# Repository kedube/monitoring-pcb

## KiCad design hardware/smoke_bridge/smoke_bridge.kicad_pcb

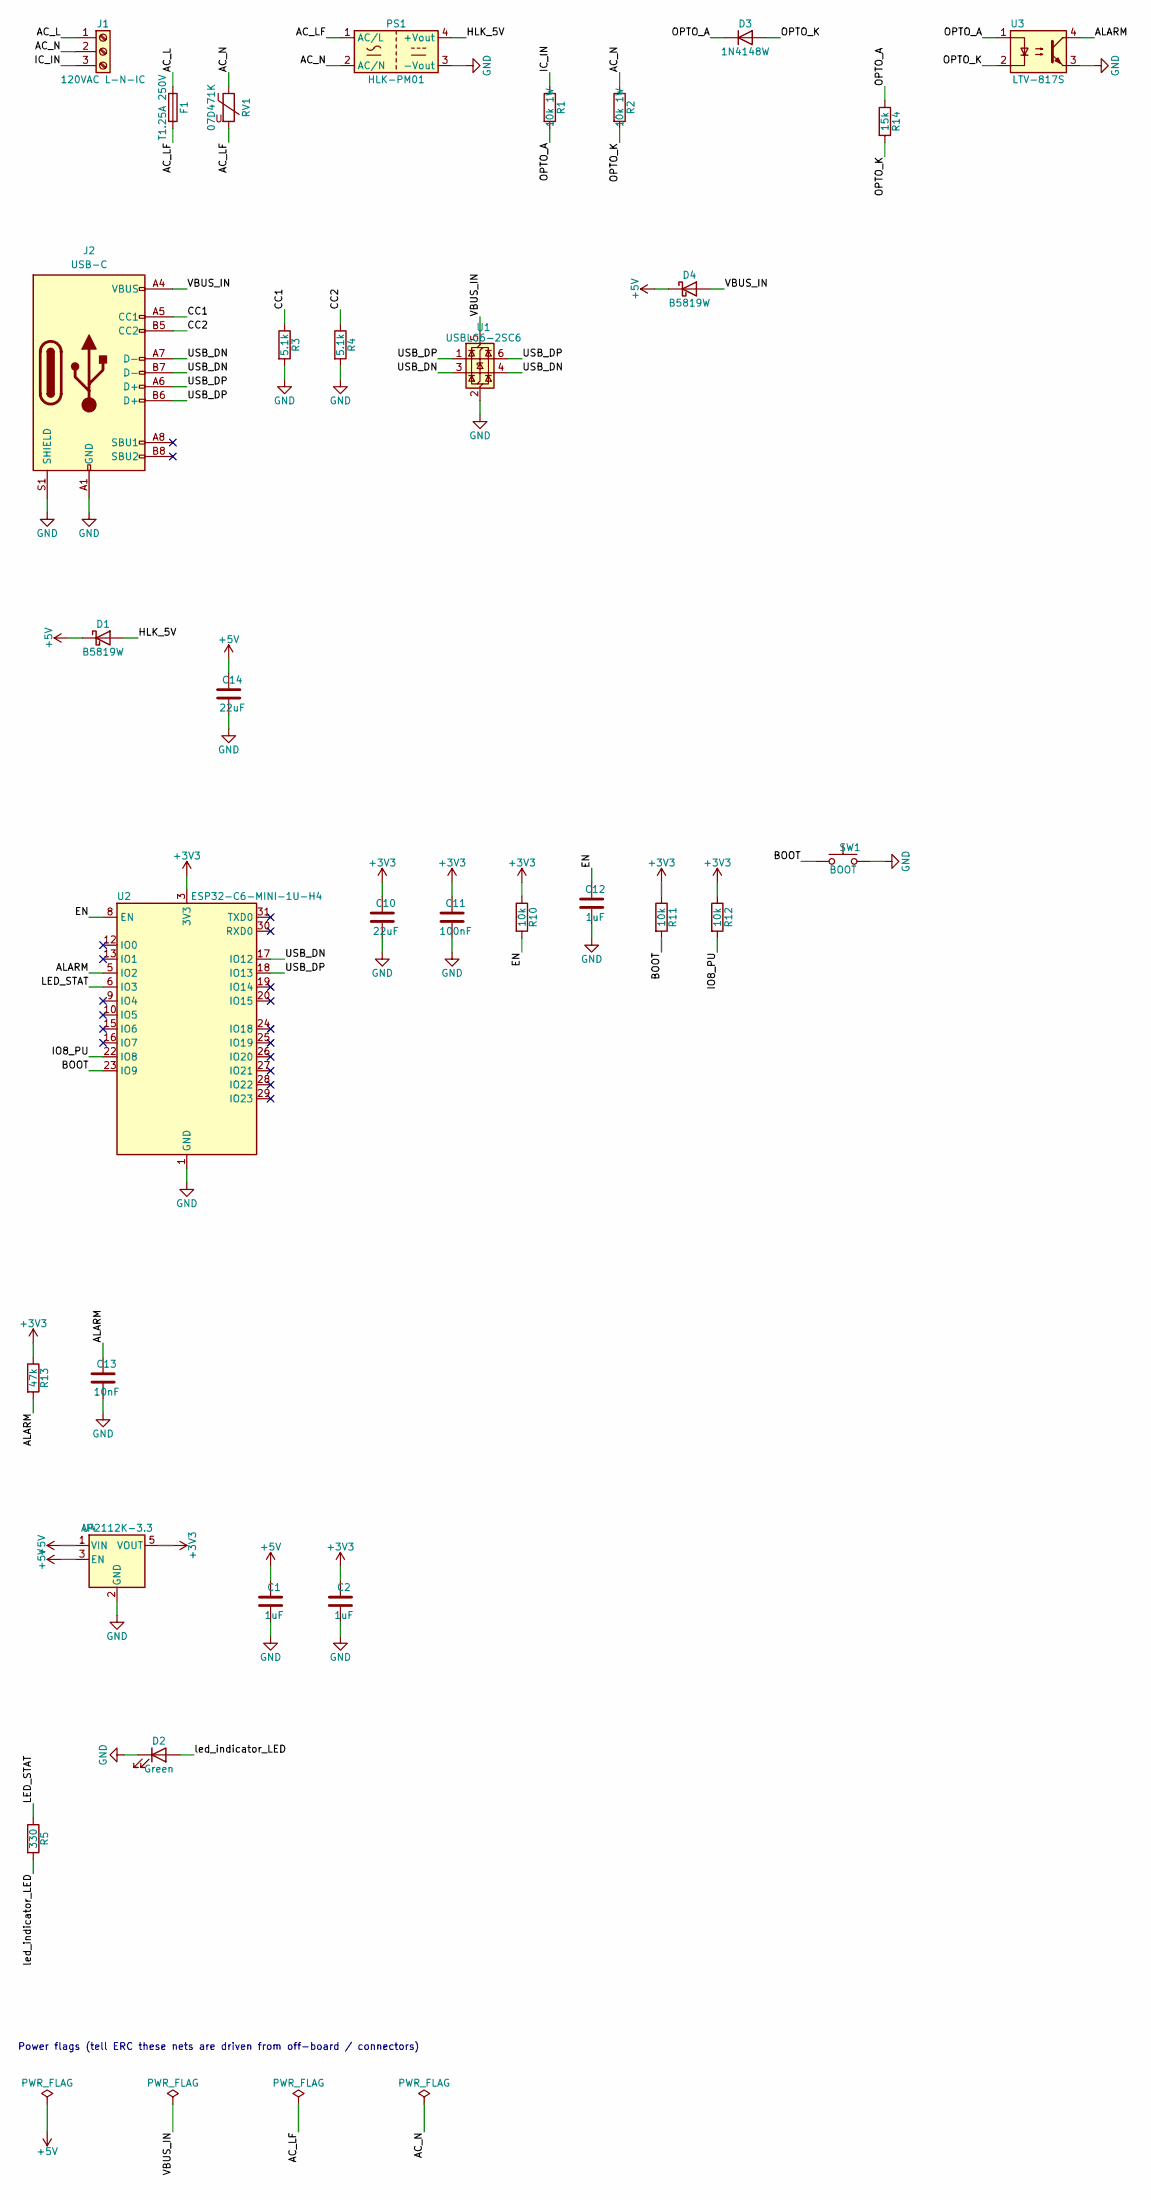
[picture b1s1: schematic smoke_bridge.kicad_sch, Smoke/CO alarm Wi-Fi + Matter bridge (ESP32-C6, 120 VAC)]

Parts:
C1, C2: 1uF; C_0603_1608Metric; LCSC C15849
C10, C14: 22uF; C_1206_3216Metric; LCSC C12891
C11: 100nF; C_0402_1005Metric; LCSC C307331
C12: 1uF; C_0402_1005Metric; LCSC C52923
C13: 10nF; C_0402_1005Metric; LCSC C15195
D1, D4: B5819W; D_SOD-123; LCSC C8598
D2: Green; LED_0805_2012Metric; LCSC C2297
D3: 1N4148W; D_SOD-123; LCSC C81598
F1: T1.25A 250V; Fuse_Littelfuse_395Series; MPN 2010T1.25A250V; LCSC C354901
J1: 120VAC L-N-IC; Terminal_3P_5.08_L-N-IC; MPN DB128L-5.08-3P-BK-S; LCSC C430602
J2: USB-C; USB_C_Receptacle_HRO_TYPE-C-31-M-12; LCSC C165948
PS1: HLK-PM01; HLK-PM01_IsolationBarrier; LCSC C209903
R1, R2: 10k 1W; R_2512_6332Metric; Voltage 200V; LCSC C25718
R3, R4: 5.1k; R_0603_1608Metric; LCSC C23186
R5: 330; R_0603_1608Metric; LCSC C23138
R10, R11, R12: 10k; R_0402_1005Metric; LCSC C25744
R13: 47k; R_0402_1005Metric; LCSC C25792
R14: 15k; R_0603_1608Metric; LCSC C22809
RV1: 07D471K; C_Disc_D7.5mm_W5.0mm_P5.00mm; LCSC C49072860
SW1: BOOT; SW_SPST_PTS810; MPN PTS810SJG250SMTRLFS; LCSC C221895
U1: USBLC6-2SC6; SOT-23-6; LCSC C7519
U2: ESP32-C6-MINI-1U-H4; ESP32-C6-MINI-1U; LCSC C20627095
U3: LTV-817S; SMDIP-4_W9.53mm; MPN LTV-817S-TA1-C; LCSC C109227
U4: AP2112K-3.3; SOT-23-5; LCSC C51118

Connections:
+3V3: C2.1, C10.1, C11.1, R10.1, R11.1, R12.1, R13.1, U2.3 (3V3), U4.5 (VOUT)
+5V: C1.1, C14.1, D1.1 (K), D4.1 (K), U4.1 (VIN), U4.3 (EN)
/AC_L: F1.1, J1.1
/AC_LF: F1.2, PS1.1 (AC/L), RV1.2
/AC_N: J1.2, PS1.2 (AC/N), R2.1, RV1.1
/ALARM: C13.1, R13.2, U2.5 (IO2), U3.4
/BOOT: R11.2, SW1.1, U2.23 (IO9)
/CC1: J2.A5 (CC1), R3.1
/CC2: J2.B5 (CC2), R4.1
/EN: C12.1, R10.2, U2.8 (EN)
/HLK_5V: D1.2 (A), PS1.4 (+Vout)
/IC_IN: J1.3, R1.1
/IO8_PU: R12.2, U2.22 (IO8)
/LED_STAT: R5.1, U2.6 (IO3)
/OPTO_A: D3.1 (K), R1.2, R14.1, U3.1
/OPTO_K: D3.2 (A), R2.2, R14.2, U3.2
/USB_DN: J2.A7 (D-), J2.B7 (D-), U1.3 (I/O2), U1.4 (I/O2), U2.17 (IO12)
/USB_DP: J2.A6 (D+), J2.B6 (D+), U1.1 (I/O1), U1.6 (I/O1), U2.18 (IO13)
/VBUS_IN: D4.2 (A), J2.A4 (VBUS), J2.A9 (VBUS), J2.B4 (VBUS), J2.B9 (VBUS), U1.5 (VBUS)
/led_indicator_LED: D2.2 (A), R5.2
GND: C1.2, C2.2, C10.2, C11.2, C12.2, C13.2, C14.2, D2.1 (K), J2.A1 (GND), J2.A12 (GND), J2.B1 (GND), J2.B12 (GND), J2.S1 (SHIELD), PS1.3 (-Vout), R3.2, R4.2, SW1.2, U1.2 (GND), U2.1 (GND), U2.2 (GND), U2.11 (GND), U2.14 (GND), U2.36 (GND), U2.37 (GND), U2.38 (GND), U2.39 (GND), U2.40 (GND), U2.41 (GND), U2.42 (GND), U2.43 (GND), U2.44 (GND), U2.45 (GND), U2.46 (GND), U2.47 (GND), U2.48 (GND), U2.49 (GND), U2.50 (GND), U2.51 (GND), U2.52 (GND), U2.53 (GND), U3.3, U4.2 (GND)

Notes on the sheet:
Power flags (tell ERC these nets are driven from off-board / connectors)

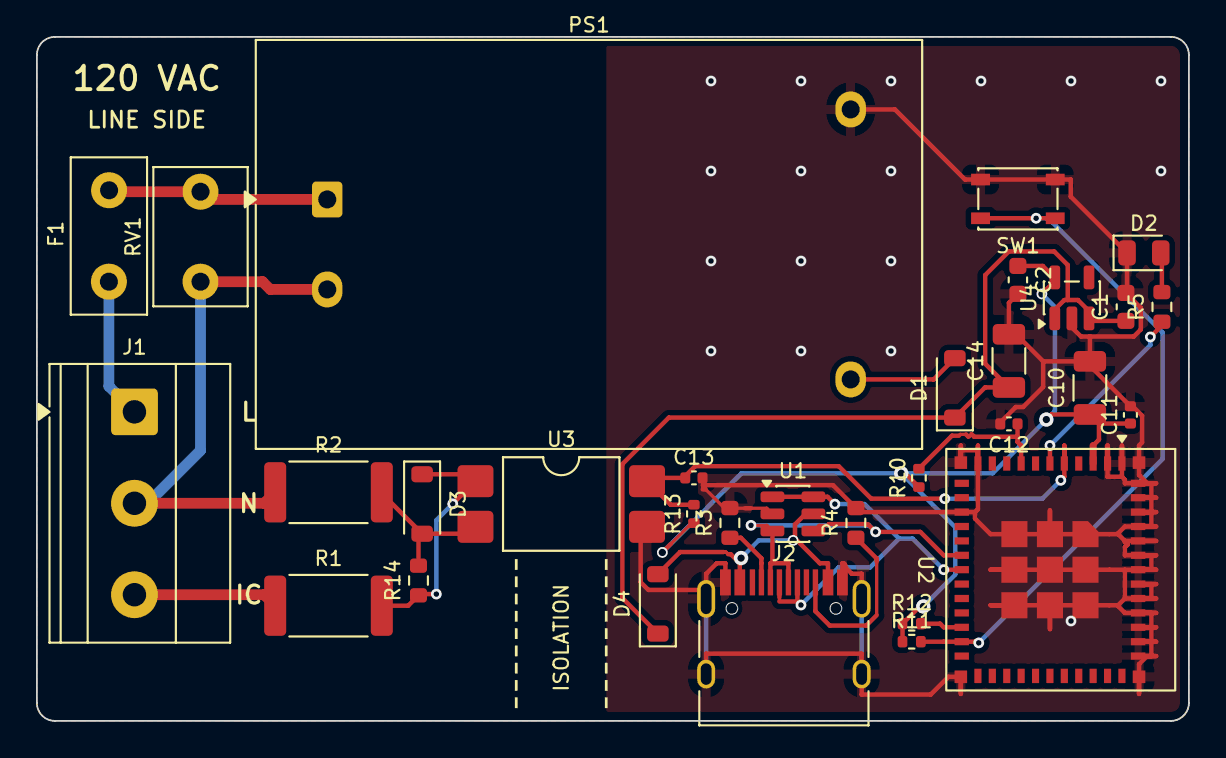
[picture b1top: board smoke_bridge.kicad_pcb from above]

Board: 2 copper layers, 64.0 x 38.0 mm, 31 parts (0 on the bottom side), 21 nets.

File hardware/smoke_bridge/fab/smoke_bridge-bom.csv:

Comment,Designator,Footprint,LCSC Part #,MPN,Qty
100nF,C11,C_0402_1005Metric,C307331,,1
1uF,C12,C_0402_1005Metric,C52923,,1
10nF,C13,C_0402_1005Metric,C15195,,1
1uF,"C1,C2",C_0603_1608Metric,C15849,,2
22uF,"C10,C14",C_1206_3216Metric,C12891,,2
Green,D2,LED_0805_2012Metric,C2297,,1
1N4148W,D3,D_SOD-123,C81598,,1
B5819W,"D1,D4",D_SOD-123,C8598,,2
T1.25A 250V,F1,Fuse_Littelfuse_395Series,C354901,2010T1.25A250V,1
120VAC L-N-IC,J1,Terminal_3P_5.08_L-N-IC,C430602,DB128L-5.08-3P-BK-S,1
USB-C,J2,USB_C_Receptacle_HRO_TYPE-C-31-M-12,C165948,,1
HLK-PM01,PS1,HLK-PM01_IsolationBarrier,C209903,,1
330,R5,R_0603_1608Metric,C23138,,1
47k,R13,R_0402_1005Metric,C25792,,1
15k,R14,R_0603_1608Metric,C22809,,1
10k 1W,"R1,R2",R_2512_6332Metric,C25718,,2
10k,"R10,R11,R12",R_0402_1005Metric,C25744,,3
5.1k,"R3,R4",R_0603_1608Metric,C23186,,2
07D471K,RV1,C_Disc_D7.5mm_W5.0mm_P5.00mm,C49072860,,1
BOOT,SW1,SW_SPST_PTS810,C221895,PTS810SJG250SMTRLFS,1
USBLC6-2SC6,U1,SOT-23-6,C7519,,1
ESP32-C6-MINI-1U-H4,U2,ESP32-C6-MINI-1U,C20627095,,1
LTV-817S,U3,SMDIP-4_W9.53mm,C109227,LTV-817S-TA1-C,1
AP2112K-3.3,U4,SOT-23-5,C51118,,1
